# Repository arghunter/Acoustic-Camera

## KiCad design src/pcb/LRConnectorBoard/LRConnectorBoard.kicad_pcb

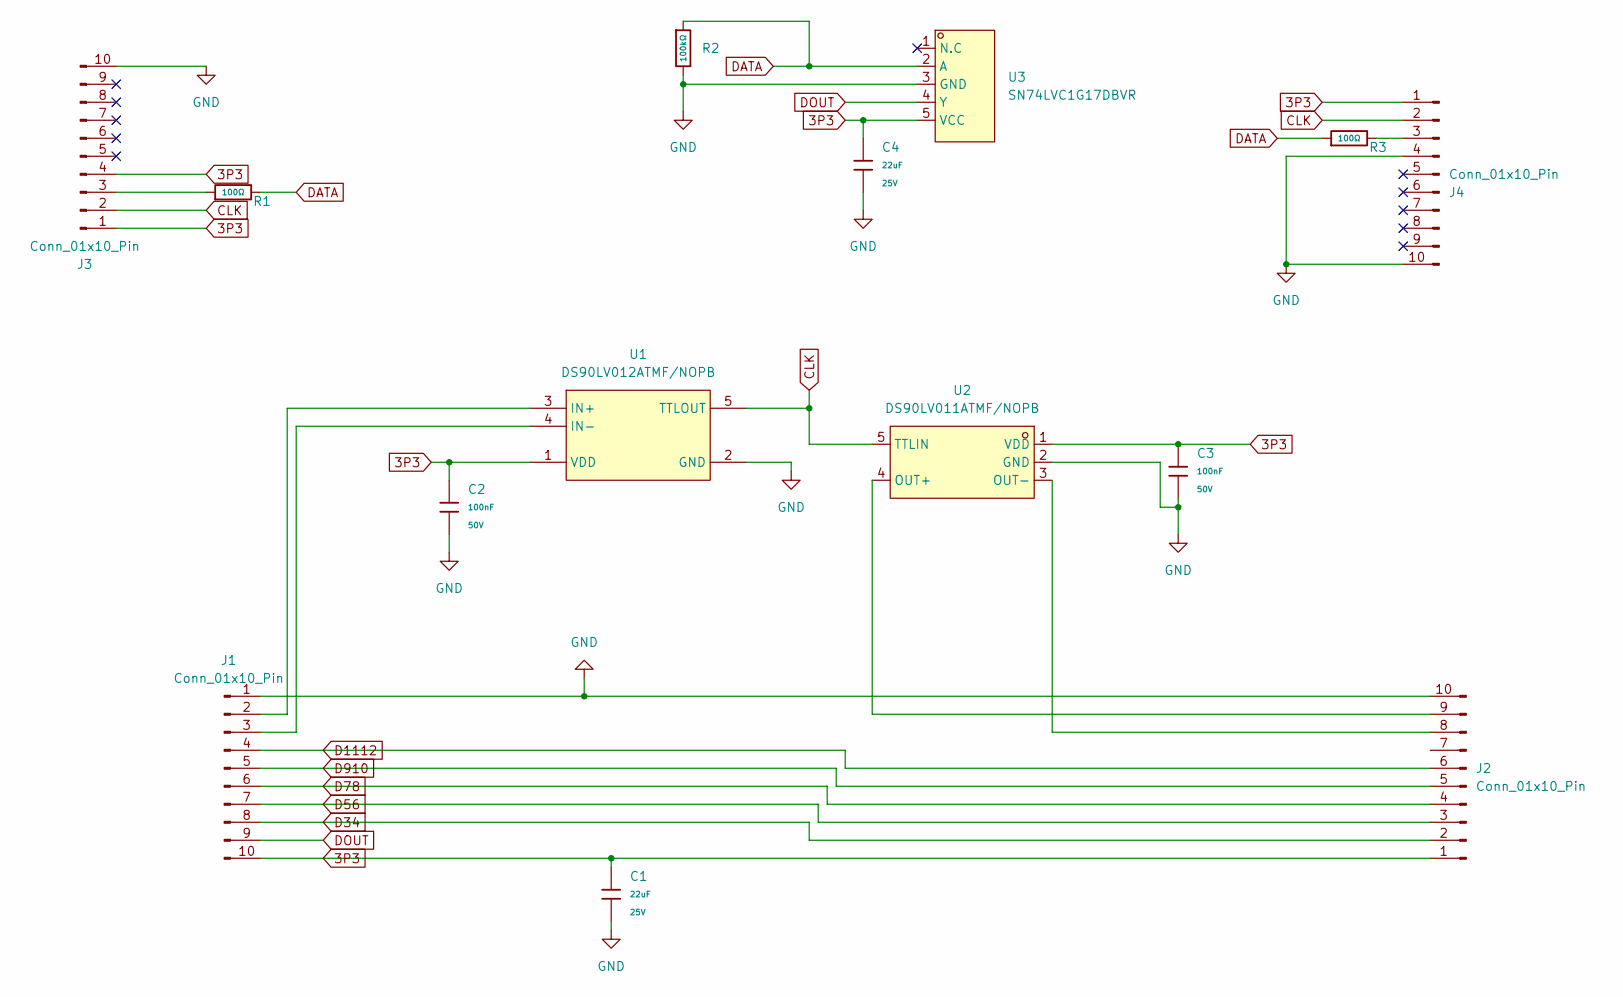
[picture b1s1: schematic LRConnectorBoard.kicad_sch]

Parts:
C1, C4: 22uF; C_0805; Voltage Rated 25V; Tolerance ±20%; Part CL21A226MAQNNNE; LCSC C45783
C2, C3: 100nF; C_0603; Voltage Rated 50V; Tolerance ±10%; Part CC0603KRX7R9BB104; LCSC C14663
J1, J2, J3, J4: Conn_01x10_Pin; FPC-SMD_F0502-B-10-10G-R
R1, R3: 100Ω; R_0603; Overload Voltage (Max) 75V; Tolerance ±1%; Part 0603WAF1000T5E; LCSC C22775
R2: 100kΩ; R_0603; Overload Voltage (Max) 75V; Tolerance ±1%; Part 0603WAF1003T5E; LCSC C25803
U1: DS90LV012ATMF/NOPB; SOT-23-5_L3.0-W1.7-P0.95-LS2.8-BR; LCSC Part C73183
U2: DS90LV011ATMF/NOPB; SOT-23-5_L2.9-W1.6-P0.95-LS2.8-BL; LCSC Part C477970
U3: SN74LVC1G17DBVR; SOT-23-5_L3.0-W1.7-P0.95-LS2.8-BR; LCSC Part C7836

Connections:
3P3: C1.1, C2.1, C3.1, C4.1, J1.10, J2.1, J3.1, J3.4, J4.1, U1.1 (VDD), U2.1 (VDD), U3.5 (VCC)
CLK: J3.2, J4.2, U1.5 (TTLOUT), U2.5 (TTLIN)
D34: J1.8, J2.2
D56: J1.7, J2.3
D78: J1.6, J2.4
D910: J1.5, J2.5
D1112: J1.4, J2.6
DATA: R1.2, R2.1, R3.1, U3.2 (A)
DOUT: J1.9, U3.4 (Y)
GND: C1.2, C2.2, C3.2, C4.2, J1.1, J1.11, J1.12, J2.10, J2.11, J2.12, J3.10, J3.11, J3.12, J4.4, J4.10, J4.11, J4.12, R2.2, U1.2 (GND), U2.2 (GND), U3.3 (GND)
unnamed: J1.2, U1.3 (IN+)
unnamed: J1.3, U1.4 (IN-)
unnamed: J2.8, U2.3 (OUT-)
unnamed: J2.9, U2.4 (OUT+)
unnamed: J3.3, R1.1
unnamed: J4.3, R3.2

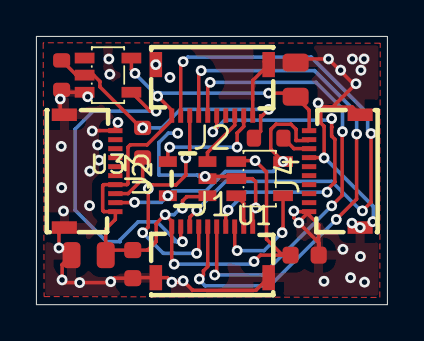
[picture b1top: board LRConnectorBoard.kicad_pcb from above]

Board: 2 copper layers, 19.5 x 14.9 mm, 14 parts (0 on the bottom side), 16 nets.

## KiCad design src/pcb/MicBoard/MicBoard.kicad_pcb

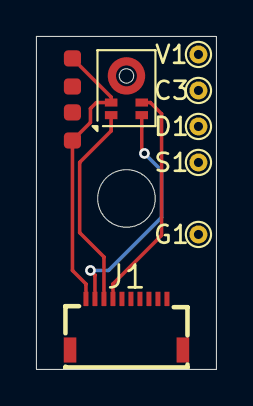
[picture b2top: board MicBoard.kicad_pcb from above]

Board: 2 copper layers, 10.0 x 18.5 mm, 9 parts (0 on the bottom side), 5 nets.

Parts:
C1: 1uF; C_0603
C2: 100nF; C_0603
C3: TestPoint; TestPoint_THTPad_D1.0mm_Drill0.5mm
D1: TestPoint; TestPoint_THTPad_D1.0mm_Drill0.5mm
G1: TestPoint; TestPoint_THTPad_D1.0mm_Drill0.5mm
J1: Conn_01x10_Pin; FPC-SMD_F0502-B-10-10G-R
MK1: IM69D120; Infineon_PG-LLGA-5-1
S1: TestPoint; TestPoint_THTPad_D1.0mm_Drill0.5mm
V1: TestPoint; TestPoint_THTPad_D1.0mm_Drill0.5mm

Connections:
3P3: C1.1, C2.1, J1.10, MK1.2 (VDD), V1.1
CLK: C3.1, J1.9, MK1.3 (CLOCK)
DATA: D1.1, J1.8, MK1.1 (DATA)
GND: C1.2, C2.2, G1.1, J1.1, MK1.5 (GND)
SEL: J1.7, MK1.4 (SELECT), S1.1

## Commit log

2025-05-31 small
2025-05-31 first schematic? maybe
2025-05-31 failing at footprints
2025-06-17 added footprints very painfully
2025-06-17 layout 1 completed
2025-06-21 finalized lyout for microphone
2025-06-23 schematic for lr connector
2025-06-29 routed the lr connector
